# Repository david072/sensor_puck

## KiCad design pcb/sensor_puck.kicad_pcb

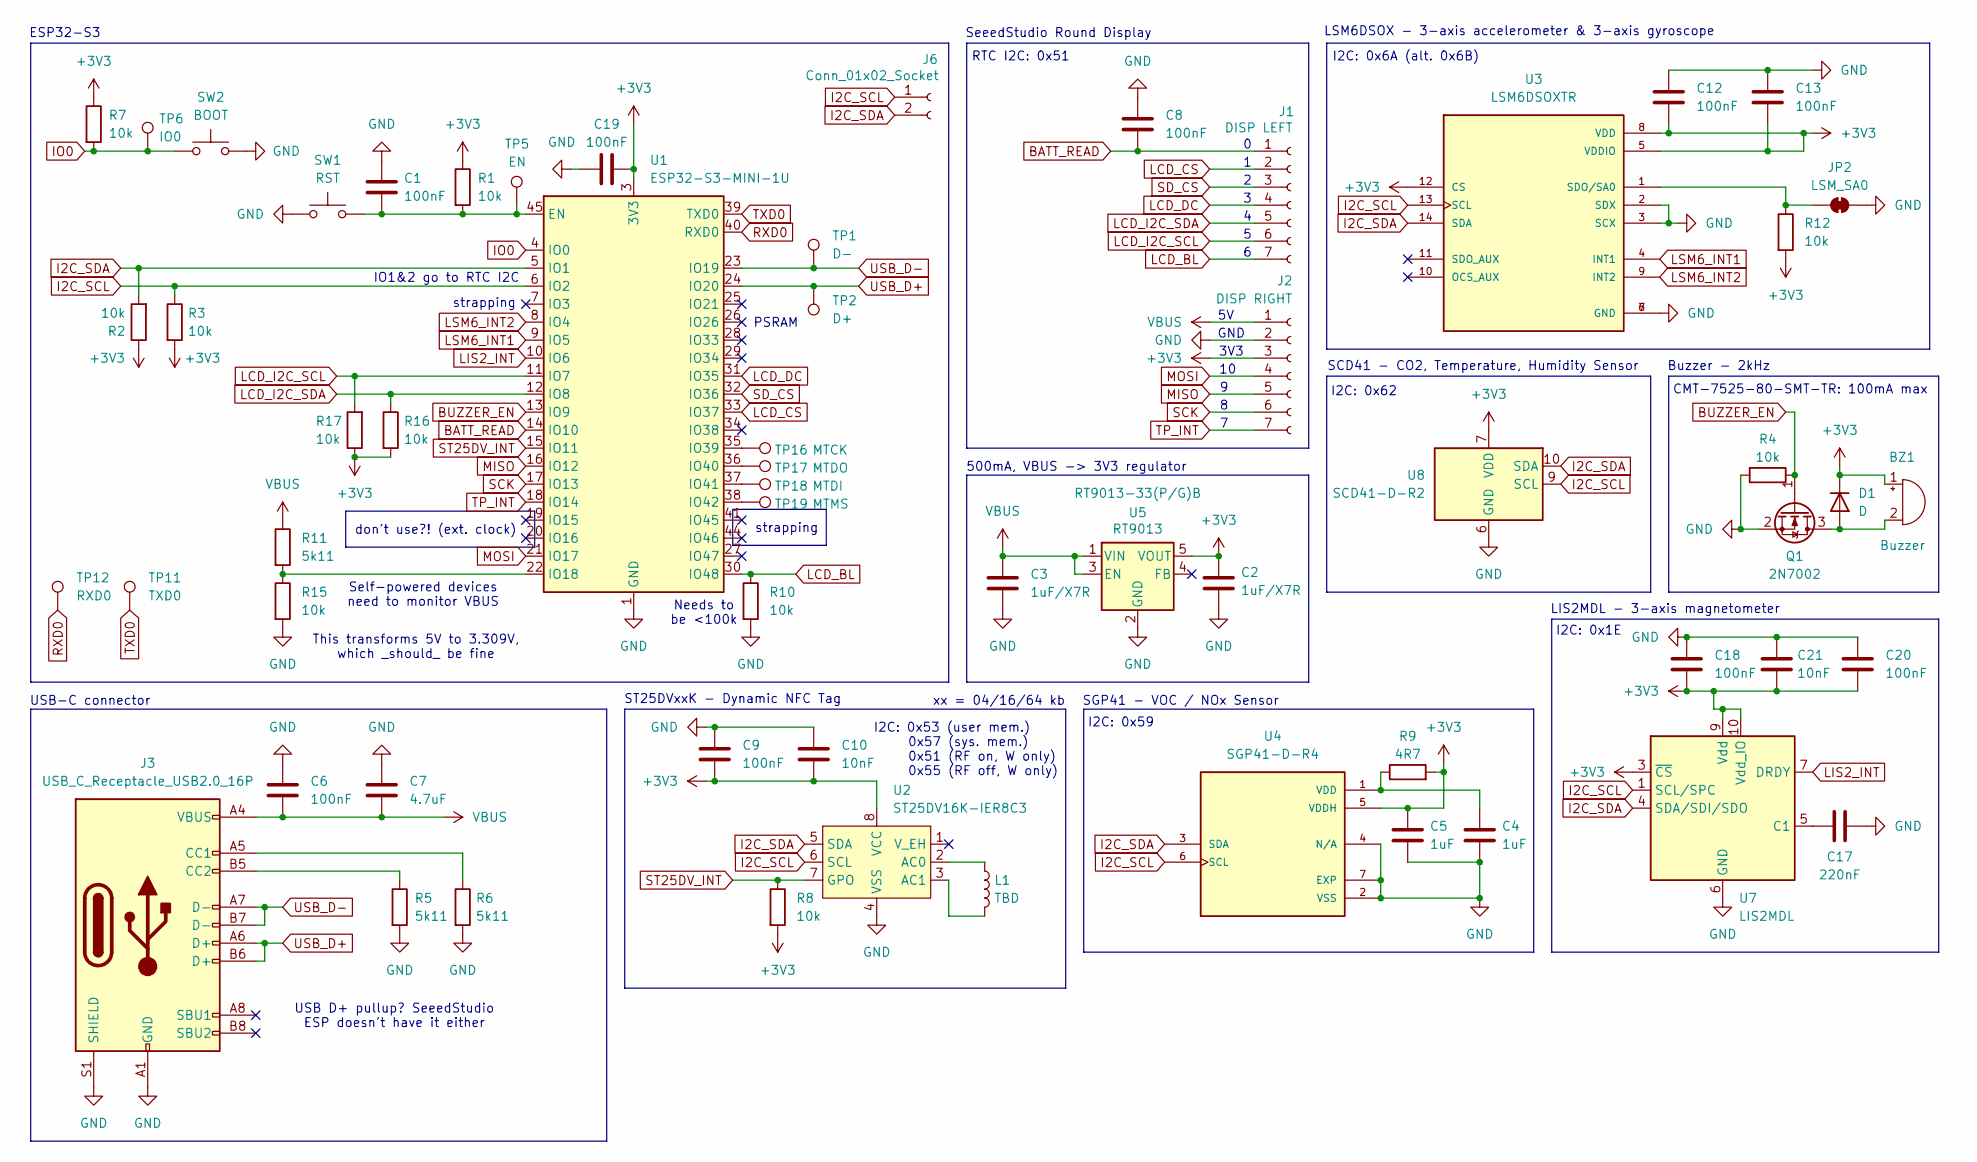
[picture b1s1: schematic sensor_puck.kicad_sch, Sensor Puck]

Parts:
BZ1: Buzzer; CMT-7525-80-SMT-TR
C1, C6, C8, C9, C12, C13, C18, C19, C20: 100nF; C_0805_2012Metric; JLCPCB Part # C1711
C2, C3: 1uF/X7R; C_0805_2012Metric; JLCPCB Part # C28323
C4, C5: 1uF; C_0805_2012Metric; JLCPCB Part # C28323
C7: 4.7uF; C_0805_2012Metric; JLCPCB Part # C1779
C10, C21: 10nF; C_0805_2012Metric; JLCPCB Part # C1710
C17: 220nF; C_0805_2012Metric; JLCPCB Part # C5378
D1: D; D_0805_2012Metric
J1: DISP LEFT; PinHeader_1x07_P2.54mm_Vertical
J2: DISP RIGHT; PinHeader_1x07_P2.54mm_Vertical
J3: USB_C_Receptacle_USB2.0_16P; USB_C_Receptacle_G-Switch_GT-USB-7010ASV; JLCPCB Part # C2988369
J6: Conn_01x02_Socket; PinHeader_1x02_P2.00mm_Vertical
JP2: LSM_SA0; SolderJumper-2_P1.3mm_Bridged_RoundedPad1.0x1.5mm
L1: TBD; PinHeader_1x02_P2.54mm_Vertical
Q1: 2N7002; SOT-23; JLCPCB Part # C8545
R1, R2, R3, R4, R7, R8, R10, R12, R15, R16, R17: 10k; R_0805_2012Metric; JLCPCB Part # C25612
R5, R6, R11: 5k11; R_0805_2012Metric; JLCPCB Part # C212414
R9: 4R7; R_0805_2012Metric; JLCPCB Part # C137423
SW1: RST; SW_Push_1P1T_NO_CK_KMR2; JLCPCB Part # C221676
SW2: BOOT; SW_Push_1P1T_NO_CK_KMR2; JLCPCB Part # C221676
TP1: D-; TestPoint_Pad_D1.0mm
TP2: D+; TestPoint_Pad_D1.0mm
TP5: EN; TestPoint_Pad_D1.0mm
TP6: IO0; TestPoint_Pad_D1.0mm
TP11: TXD0; TestPoint_Pad_D1.0mm
TP12: RXD0; TestPoint_Pad_D1.0mm
TP16: MTCK; TestPoint_Pad_D1.0mm
TP17: MTDO; TestPoint_Pad_D1.0mm
TP18: MTDI; TestPoint_Pad_D1.0mm
TP19: MTMS; TestPoint_Pad_D1.0mm
U1: ESP32-S3-MINI-1U; ESP32-S2-MINI-1U
U2: ST25DV16K-IER8C3; DFN-8-1EP_3x2mm_P0.5mm_EP1.36x1.46mm
U3: LSM6DSOXTR; LGA-14_3x2.5mm_P0.5mm_LayoutBorder3x4y; PARTREV 3.0
U4: SGP41-D-R4; XDCR_SGP41-D-R4; PARTREV 1.0
U5: RT9013; SOT-23-5; JLCPCB Part # C47773
U7: LIS2MDL; LGA-12_2x2mm_P0.5mm
U8: SCD41-D-R2; Sensirion_SCD4x-1EP_10.1x10.1mm_P1.25mm_EP4.8x4.8mm

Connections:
+3V3: BZ1.1 (+), C2.2, C5.1, C9.2, C10.2, C12.2, C13.2, C18.1, C19.2, C20.1, C21.1, D1.1 (K), J2.3, R1.1, R2.1, R3.2, R7.1, R8.2, R9.2, R12.2, R16.2, R17.1, U1.3 (3V3), U2.8 (VCC), U3.5 (VDDIO), U3.8 (VDD), U3.12 (CS), U4.5 (VDDH), U5.5 (VOUT), U7.3 (~CS), U7.9 (Vdd), U7.10 (Vdd_IO), U8.7 (VDD), U8.19 (VDD)
BATT_READ: C8.1, J1.1, U1.14 (IO10)
BUZZER_EN: Q1.1 (G), R4.1, U1.13 (IO9)
GND: C1.1, C2.1, C3.1, C4.2, C5.2, C6.1, C7.1, C8.2, C9.1, C10.1, C12.1, C13.1, C17.2, C18.2, C19.1, C20.2, C21.2, J2.2, J3.A1 (GND), J3.A12 (GND), J3.B1 (GND), J3.B12 (GND), J3.S1 (SHIELD), JP2.2 (B), Q1.2 (S), R4.2, R5.2, R6.2, R10.2, R15.2, SW1.1, SW2.2, U1.1 (GND), U1.2 (GND), U1.42 (GND), U1.43 (GND), U1.46 (GND), U1.47 (GND), U1.48 (GND), U1.49 (GND), U1.50 (GND), U1.51 (GND), U1.52 (GND), U1.53 (GND), U1.54 (GND), U1.55 (GND), U1.56 (GND), U1.57 (GND), U1.58 (GND), U1.59 (GND), U1.60 (GND), U1.61 (GND), U1.62 (GND), U1.63 (GND), U1.64 (GND), U1.65 (GND), U2.4 (VSS), U3.2 (SDX), U3.3 (SCX), U3.6 (GND), U3.7 (GND), U4.2 (VSS), U4.4 (N/A), U4.7 (EXP), U5.2 (GND), U7.6 (GND), U7.8 (GND), U8.6 (GND), U8.20 (GND), U8.21 (GND)
I2C_SCL: J6.1, R3.1, U1.6 (IO2), U2.6 (SCL), U3.13 (SCL), U4.6 (SCL), U7.1 (SCL/SPC), U8.9 (SCL)
I2C_SDA: J6.2, R2.2, U1.5 (IO1), U2.5 (SDA), U3.14 (SDA), U4.3 (SDA), U7.4 (SDA/SDI/SDO), U8.10 (SDA)
IO0: R7.2, SW2.1, TP6.1, U1.4 (IO0)
LCD_BL: J1.7, R10.1, U1.30 (IO48)
LCD_CS: J1.2, U1.33 (IO37)
LCD_DC: J1.4, U1.31 (IO35)
LCD_I2C_SCL: J1.6, R17.2, U1.11 (IO7)
LCD_I2C_SDA: J1.5, R16.1, U1.12 (IO8)
LIS2_INT: U1.10 (IO6), U7.7 (DRDY)
LSM6_INT1: U1.9 (IO5), U3.4 (INT1)
LSM6_INT2: U1.8 (IO4), U3.9 (INT2)
MISO: J2.5, U1.16 (IO12)
MOSI: J2.4, U1.21 (IO17)
unnamed: BZ1.2 (-), D1.2 (A), Q1.3 (D)
unnamed: J3.A5 (CC1), R6.1
unnamed: J3.B5 (CC2), R5.1
unnamed: JP2.1 (A), R12.1, U3.1 (SDO/SA0)
unnamed: C1.2, R1.2, SW1.2, TP5.1, U1.45 (EN)
unnamed: R11.2, R15.1, U1.22 (IO18)
unnamed: TP16.1, U1.35 (IO39)
unnamed: TP17.1, U1.36 (IO40)
unnamed: TP18.1, U1.37 (IO41)
unnamed: TP19.1, U1.38 (IO42)
unnamed: L1.1, U2.2 (AC0)
unnamed: L1.2, U2.3 (AC1)
unnamed: C4.1, R9.1, U4.1 (VDD)
unnamed: C17.1, U7.5 (C1)
RXD0: TP12.1, U1.40 (RXD0)
SCK: J2.6, U1.17 (IO13)
SD_CS: J1.3, U1.32 (IO36)
ST25DV_INT: R8.1, U1.15 (IO11), U2.7 (GPO)
TP_INT: J2.7, U1.18 (IO14)
TXD0: TP11.1, U1.39 (TXD0)
USB_D+: J3.A6 (D+), J3.B6 (D+), TP2.1, U1.24 (IO20)
USB_D-: J3.A7 (D-), J3.B7 (D-), TP1.1, U1.23 (IO19)
VBUS: C3.2, C6.2, C7.2, J2.1, J3.A4 (VBUS), J3.A9 (VBUS), J3.B4 (VBUS), J3.B9 (VBUS), R11.1, U5.1 (VIN), U5.3 (EN)

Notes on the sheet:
LIS2MDL - 3-axis magnetometer
USB-C connector
strapping
I2C: 0x59
I2C: 0x53 (user mem.) 0x57 (sys. mem.) 0x51 (RF on, W only) 0x55 (RF off, W only)
ESP32-S3
Buzzer - 2kHz
This transforms 5V to 3.309V, which _should_ be fine
SeeedStudio Round Display
xx = 04/16/64 kb
Needs to be <100k
I2C: 0x1E
RTC I2C: 0x51
PSRAM
USB D+ pullup? SeeedStudio ESP doesn't have it either
I2C: 0x6A (alt. 0x6B)
don't use?! (ext. clock)
CMT-7525-80-SMT-TR: 100mA max
SCD41 - CO2, Temperature, Humidity Sensor
GND
Self-powered devices need to monitor VBUS
LSM6DSOX - 3-axis accelerometer & 3-axis gyroscope
IO1&2 go to RTC I2C
ST25DVxxK - Dynamic NFC Tag
3V3
I2C: 0x62
SGP41 - VOC / NOx Sensor
500mA, VBUS -> 3V3 regulator

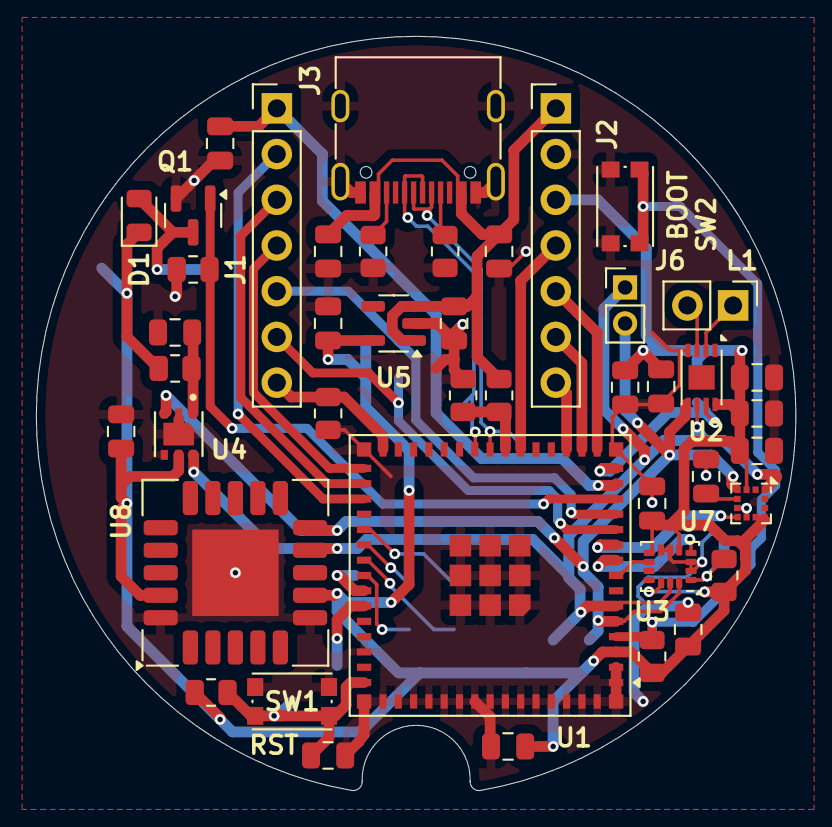
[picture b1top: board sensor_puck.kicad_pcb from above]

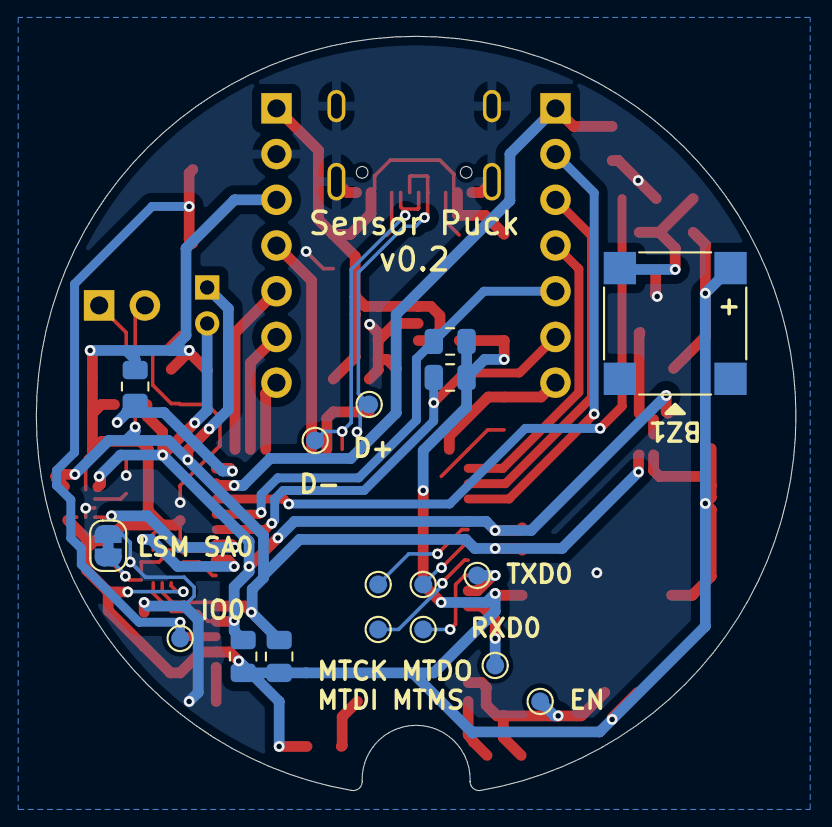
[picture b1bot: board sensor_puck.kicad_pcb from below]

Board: 2 copper layers, 42.2 x 41.9 mm, 60 parts (17 on the bottom side), 40 nets.

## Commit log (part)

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2024-10-11 feat: air-quality page
2024-10-11 feat: basic clock/home page
2024-10-11 feat: compass page
2024-10-27 feat: add PCB design files
2024-10-28 fix(pcb): more changes
2024-11-05 feat(pcb): route PCB
2024-11-21 feat(ui): sync system time and RTC time and use LVGL timers for UI update
2024-11-22 feat: idrk
2024-11-23 refactor: make rotary input system nicer
2024-11-23 feat: allow setting the system and RTC clock's time
2024-11-23 feat(RotaryInputPage): customizable value label formatting
2024-11-24 refactor: move ClockSettingsPage into ClockPage
2024-11-24 fix(Vector3): make constructors and methods constexpr
2024-11-24 feat: timer overlay
2024-11-24 fix: add note for battery voltage reading
2024-11-24 chore: put constants (pins, I2C addresses, etc.) into a dedicated file
2024-11-25 fix(pcb): add pulldown for LCD_BL pin
2024-11-25 feat: keep track of timer while in deep-sleep
2024-11-25 feat: display sensor data faster after boot
2024-11-27 fix: improve battery charge calculation
2024-11-30 chore: re-add PCB files from PIO project
2024-11-30 feat: move BM8563 driver into a separate component
2024-12-01 fix: give LSM read task the same priority as LVGL
2024-12-01 feat: use std::function for update label callback
2024-12-04 fix(BM8563): correctly write data
2024-12-05 feat: basic Bluetooth LE interface
2024-12-05 feat: basic Flutter App communicating via BLE
2024-12-05 feat(BluetoothPeripheralManager): track connected status
2024-12-05 feat(SettingsPage): debounce Bluetooth checkbox
2024-12-07 feat: wifi
2024-12-07 feat(wifi): I'm going absolutely insane
2024-12-26 feat: improve deep-sleep wakeup time (fast boot)
2024-12-26 chore(schematic): use LIS2MDL instead of LIS3MDL
    Since the LIS3MDL is now NRND (approaching EOL), we should use a
    different magnetometer. The LIS2MDL seems to be a close replacement
    here, also offering 3-axis magnetic sensing.
2024-12-27 feat(schematic): add resettable fuses to VBUS and 3V3 for short protection
2024-12-28 feat: constrain minimum SDG duration
2025-01-15 feat: use SCD41 CO2 sensor
2025-01-15 wip: wifi things idk
2025-01-15 refactor: use Sensirion library for SCD41
2025-01-17 feat: use ULP RISC-V coprocessor to continue monitoring CO2 during deep sleep
    We now use the ULP (Ultra Low Power) RISC-V coprocessor to continue
    monitoring the CO2 PPM level using the SCD41 I2C sensor. We do this by
    bit banging the I2C protocol onto the SCL and SDA pins, since they are
    connected to RTC pins, but not the the specific ones that the RTC I2C
    peripheral could use. I believe in its current, very basic
    implementation we get about 33kHz clock frequency out of that. The ULP
2025-01-17 fix(schematic): connect I2C lines to RTC I2C peripheral
2025-01-18 feat(schematic): connect display using separate I2C bus
    Since we're polling at least the LSM very fast, the constantly busy bus
    might cause us to detect touch slower, thereby making the user
    experience with the display worse. By putting the touch screen sensor
    onto its own I2C bus, we might be able to avoid this. Note that this
    works, since the ESP has two I2C controllers, that can be routed to any
    pin (as far as I understand).
2025-01-18 fix: use correct wakeup cause for wakeups caused by ULP RISC-V
2025-01-27 fix: filter rapid movement on display
    We now filter movement that is too quick to be valid movement by the
    user on the display, and instead return the previously recorded pointer
    position again. This seems to make movement on the display more stable
    and prevents incorrect readings by the touch screen controller causing
    weird jumping of the UI.
2025-01-27 refactor: remove manual I2C lock
    All I2C APIs provided by ESP-IDF are already thread-safe, either
    guaranteed by the I2C-peripheral or abstracted in the library.
2025-01-29 feat(scd): use normal periodic measurement
    This does use about three times more current than the lower power
    variant, however it allows us to get a new measurement every 5 seconds,
    which might increase precision in the long run (letting the sensor run
    moreo ften seems to help).
    It needs to be observed how severely this impacts battery life.
2025-01-29 feat(scd): remember measurement values using ULP variables
    By writing the last measurements to the ULP variables (when
    initialized), we immediately have values after booting again, even if
    the ULP processor didn't run yet.
2025-01-30 fix: immediately update UI on startup
    Before, we had to wait for each page's timer period to pass, before the
    page's update() method would be called the first time. This added
    unnecessary wait time for the user, before they could see any values
    on the screen. Now, we call update immediately, as soon as the LVGL task
    runs again. By assigning the saved measurements from the ULP processor
    before initializing the UI, the user can see measurements immediately
2025-01-30 fix(schematic): add pullups to LCD I2C lines
2025-02-01 refactor: redesign UI to make it easier to use for the user
2025-02-01 feat: indicate severity of the current CO2 level
2025-02-01 feat: use SCD41's humidity measurement
2025-02-02 refactor: move user timer handling into separate class
2025-02-02 fix: immediately return in ULP processor after waking up main CPU
2025-02-06 feat: add settings screen with date and time settings
2025-02-16 feat: software reset LSM6DSOX on startup
2025-02-16 fix: properly display timer overlay after sleep
    We now initialize the UI in the main task again, to make sure the timer
    started event triggered by sleep recovery is noticed by the
    TimerOverlay, thereby making it display itself properly.
2025-02-17 feat: power sensors down when entering deep sleep
    This commit introduces a system for tasks to register themselves as
    needing to do work in order to prepare for entering deep sleep. When
    display inactivity is triggered, we then wait for those tasks to do
    their work before entering deep sleep. This allows us to tell the
    sensors to power down and thus draw less current while sleeping and
    thereby not in use.
2025-02-22 feat: update firmware for new PCB
2025-02-23 feat(compass): show angular offset of device
    The compass now has as small circle in the middle that moves depending
    on the angle of the device. When the device is parallel to the ground,
    the circle will be in the middle and will move outwards the more the
    device is rotated. This currently does not show the actual angle.
2025-02-24 feat: use different battery icons for different charge levels
2025-02-25 feat: forward ESP events to LVGL
    The LVGL task now listens for all ESP events in the data event group and
    forwards them onto a dummy UI object. That way, UI elements can listen
    for events without having to deal with the ESP event loop (and
    subsequent LVGL locking, etc.) and can e.g. use events to react to data
    being updated, without having to run an update loop all the time,
    wasting processing time if nothing changed.
2025-02-25 chore: move UI initialisation into LVGL task and comment LVGL lock out
2025-02-25 fix: use correct pin for battery voltage measurement
2025-03-01 feat: disable buzzer when device is upside down
    We now use the accelerometer to detect whether the device is upside down
    by checking for vertical acceleration and if it is, we don't activate
    the buzzer.
2025-03-03 feat: use NFC chip to make URL with current sensor values available
    The Sensor Puck will now update the NFC chip every 30s with a URL that
    contains the current sensor values. In the future, this will include
    more data, such as a history of the values. This allows the user to see
    the data on a larger screen (i.e. their smartphone), as well as
    additional information (e.g. a history) that isn't really displayable on
    the small screen of the puck.
2025-03-04 feat: basic Flutter website to see data via NFC
    This website is hosted via Firebase Hosting and expects the encoded data
    via a URL parameter. It then simply displays those values.
2025-03-04 fix: prevent race conditions when waking up due to the timer expiring
    Previously, we would deliberately initialize the UI before checking
    whether the timer expired to allow it to react and give visual feedback.
    However, since the UI is initialized in the LVGL task, there was a
    chance that we would dispatch the timer expired event before the UI was
    ready to react to it. Now, the init_display() function, which starts the
    LVGL task, waits for the task to signal readiness, before returning,
2025-03-04 fix: wait for deep sleep preparation before clearing the display
    Previously, sometimes when waking the puck up, you would still see a
    sliver of the previously displayed frame. My guess is that this is
    because the LVGL task is pushing another frame to the display after we
    have already cleared it in preparation for deep sleep, making it briefly
    visible on wakeup. Since the LVGL task is integrated in the deep sleep
    preparation mechanism, we just need to wait for that to finish, before
2025-03-05 fix(ui): prevent UI from displaying incorrect values if none are available yet
    If no measurement values are available yet, we would display the default
    initialisation from Data, which is obviously not a correct value. Now,
    we don't immediately update the UI, but instead use the event system to
    react to new values being available and display placeholders that show
    that no data is available yet while waiting.
2025-03-05 feat: save whether the device is muted in NVS
    This introduces a new Preferences API to save key value pairs based on
    the existing ESP-IDF NVS API. Currently, it is very bare bones and can
    be expaned to support more data types, etc. when needed. For now it is
    used to store the "muted" status as a bool.
2025-03-10 fix(ST25DV): only write in 255 byte blocks via I2C
2025-03-10 feat: include history in NFC URL
    The NFC URL now includes a history for each sensor value. This is done
    using the FAT filesystem, where we save the set of values every 30min,
    accumulating at max 24 values. This way, the user can see some
    additional data via the NFC interface that isn't visible on the screen
    directly.
2025-03-12 refactor: stop using ULP RISC-V and wake the main CPU for periodic checks
    In the past, the experience with the ULP RISC-V coprocessor has not been
    great. The build system feels sketchy (I cannot remove anything using
    the volatile variables orelse the variable definitions are not available
    in the main project anymore) and it just straight up stopped working a
    bit ago when removing code that really shouldn't have anything to do
    with it (as far as I can tell...).
2025-03-12 fix(web): properly handle empty history
2025-03-13 fix: power SCD down when going back to sleep after environment check
2025-03-14 fix: properly size raw NFC data buffer
2025-03-15 fix: wait for data to be available before updating history
2025-03-15 refactor(web): small cleanup in HistoryPainter
2025-03-15 fix(web): show fractional minutes for hours in HistoryPainter
2025-03-16 refactor: use IAQ instead of comparing raw PPM values
2025-04-07 feat: merge SCD41 and SGP41 components
2025-04-08 feat: basic stopwatch
